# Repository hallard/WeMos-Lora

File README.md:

# ESP8266 WeMos Shield for HopeRF RFM95 RFM96 RFM98 Lora Modules

This shield is used to hold HopeRF [Lora module][4] Software with WeMos ESP8266 boards it has just few minimal features. 
- I2C Pullups placement
- Classic I2C 128x64 OLED connector
- Placement for RFM95/96/98 Lora module
- Placement for choosing single Wire, SMA or u-FL Antenna type 
- 2 x WS2812B Type LED for visual indication
- Custom switch on GPIO2
- Added footprint for Microchip 24AA02E64 64 bits serial number (v1.1+) 
- Added Solder PAD jumper to be able to connect GPIO16 to Reset to enable deep sleep (V1.2+)

You can find more information on WeMos D1 mini boards ([mini][1], [mini pro][7], [mini lite][8]), it's really well documented.
I now use WeMos boards instead of NodeMCU's one because they're just smaller, features remains the same, but I also suspect WeMos regulator far better quality than the one used on NodeMCU that are just fake of originals AMS117 3V3.

Boards arrived, I tested them, works fine with forked version of [single Channel LoRaWAN Gateway][5] but you can use any program that is compatible with RFM95 Lora module according it to real pinout.

## Detailed Description

Look at the schematics for more informations.

SPI connexion is classic (MOSI/MISO/CLK), 

**New v1.3** Solder pad on bottom layer to be able to switch 3V3 and GND Pin. It's configured as old version mapping by default (silkscreen is correct). 

Since V1.2, chip Select is still connected with GPIO16 by default but solder pad on bottom of the board allow you to connect GPIO16 to RESET for Deep Sleep. In this case: 

- add and solder R3 Pulldown (100K) to make RFM95 SPI device always selected
- on bottom solder pad cut trace between GPIO19 and SEL 
- on bottom solder join GPIO16 and RST with solder

Other pins that may need be adapted into code (for example if you use TTN network gateway code) according to the following pinout

Please not that to avoid 3 GPIOs for DIO0,DIO1,DIO2 Interrupt, these 3 are OR'ed with 3 diodes, respectively named D2,D3 and D4. This permit to use only one IRQ pin (here GPIO15). This is only possible because on IRQ routine the RFM9x IRQ register is read and then software knows which one has been triggered.
You can see more details ont this dedicated LMIC [Pull Request][6]

```
   WeMos D1          RFM9x Module
  GPIO12 (D6) <----> MISO
  GPIO13 (D7) <----> MOSI
  GPIO14 (D5) <----> CLK
  GPIO15 (D8) <----> DIO0/D2 OR DIO1/D3 OR DIO2/D4
  GPIO16 (D0) <----> SEL Chip Select (depending on bottom solder PAD position)

   WeMos D1         Shield Feature
  GPIO5  (D1) <----> I2C SCL
  GPIO4  (D2) <----> I2C SDA
  GPIO0  (D3) <----> WS2812 LEDS
  GPIO2  (D4) <----> Push Button
  GPIO16 (D0) <----> RESET (depending on bottom solder PAD position)
```

## Schematic  

## Bill Of Material

Nothing fancy, all components are 0805 and/or PTH and can be ordered almost anywhere (digikey, mouser, radiospare, ...). 
use only what you need dependings on what you want to do. You can find lot of components on ebay or aliexpress, but since vendors are often ephemere, I put for reference the BOM on well known providers.

Here is the [octopart BOM](https://octopart.com/bom-tool/SJPhS5Am)

## Firmware  

[firmware](https://github.com/hallard/WeMos-Lora/tree/master/firmware)  

## Boards  

&nbsp;

~~You can order the PCB of this board at [PCBs.io][3] if you do so, PCBs.io give me discount that allow me to buy some new created boards.~~
   
Looks like PCBs.io is gone, I do not have any rewards from PCBs.io since August 2020 and my free order placed after are still not received, so my guess they are not on business anymore.

So you can order the board on [oshpark](https://oshpark.com/shared_projects/E9P1U0Ae). It's a pitty after several discuss with OSHPark that I can't have any rewards for each people ordering my boards, this would allow me to order free PCB for shared projects and create new ones. For information my shared boards generated a total of **$285 162.00** orders at PCBs.io in 4 years, not bad at all :-)

Hoping one day OSHparks will thanks me giving them this market. 

## Assembled boards (V1.0)

## License

This work is licensed under a [Creative Commons Attribution-NonCommercial-ShareAlike 4.0 International License](https://creativecommons.org/licenses/by-nc-sa/4.0/)    
If you want to do commercial stuff with this project, please contact [CH2i company](https://www.ch2i.eu/en#support) so we can organize an simple agreement.

# Misc

See news and other projects on my [blog][2] 
 
[1]: https://wiki.wemos.cc/products:d1:d1_mini
[2]: https://hallard.me
[3]: https://PCBs.io/share/4Q1Z4 
[4]: http://www.hoperf.com/rf_transceiver/lora/
[5]: https://github.com/hallard/ESP-1ch-Gateway/
[6]: https://github.com/matthijskooijman/arduino-lmic/pull/34
[7]: https://wiki.wemos.cc/products:d1:d1_mini_pro
[8]: https://wiki.wemos.cc/products:d1:d1_mini_lite

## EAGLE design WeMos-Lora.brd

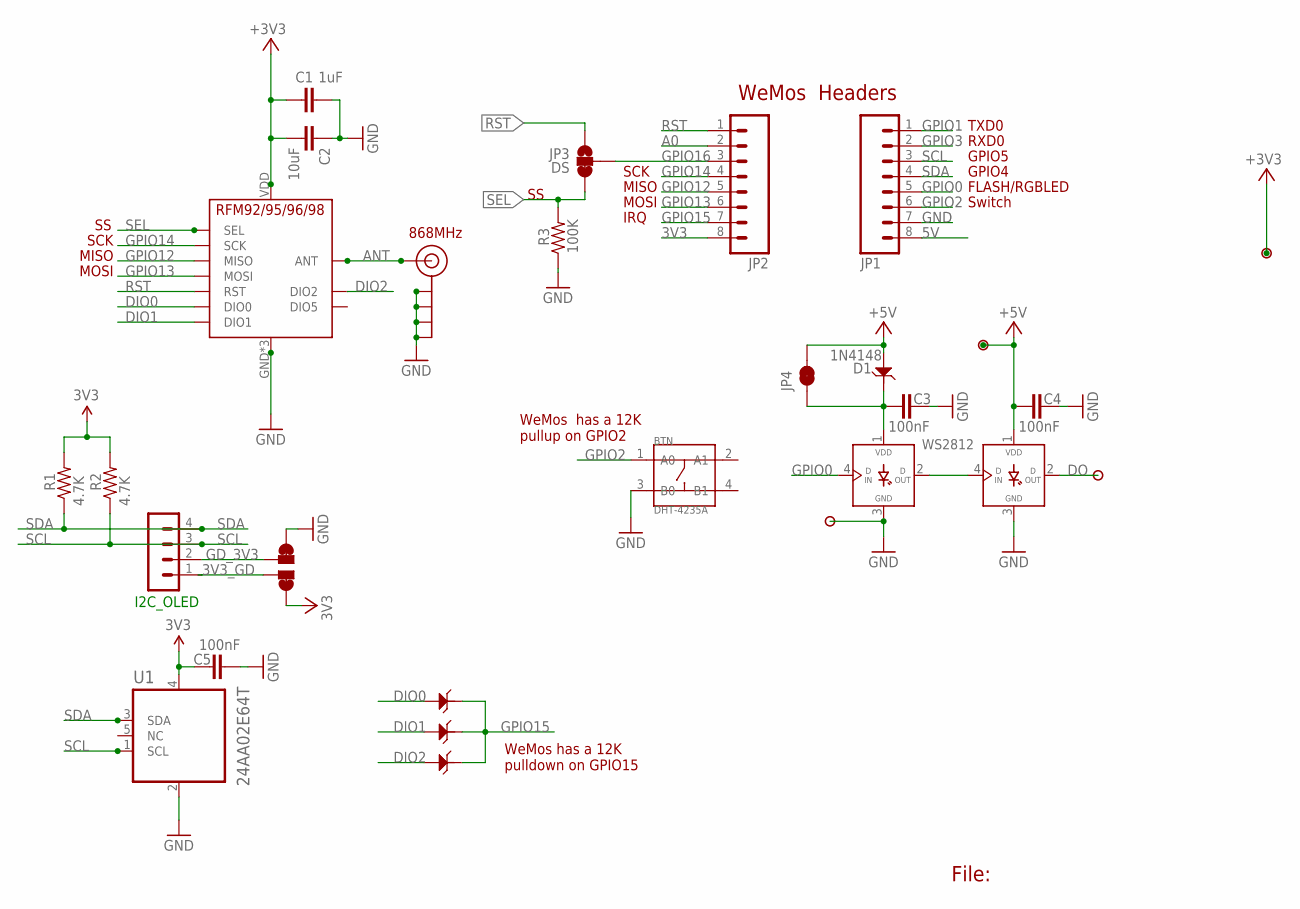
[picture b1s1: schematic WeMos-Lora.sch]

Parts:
BTN: DHT-4235A; SW4-SMD-4.2X3.2X2.5MM
C1: 1uF; 0805-CAP-LARGEPADS
C2: 10uF; 0805-CAP-LARGEPADS
C3, C4, C5: 100nF; 0805-CAP
D1, D2, D3, D4: 1N4148; SOD123-2.7X1.6
I2C_OLED: CON_HEADER_1X04'LOCK'; 1X04_LOCK
J$2: ANTENNATINY; SMA_UFL_PAD_TINY
JP1, JP2: M08NO_SILK_FEMALE_PTH; 1X08_NO_SILK
JP3: DS; PAD-JUMPER-3-2OF3_NC_BY_TRACE_YES_SILK_FULL_BOX
JP4: JUMPER-PAD-2-NC_BY_TRACE; PAD-JUMPER-2-NC_BY_TRACE_YES_SILK
P1, P2, P3, P4: PADNORMAL; PAD
R1, R2: 4.7K; 0805-RES
R3: 100K; 0805-RES
U1: 24AA02E64T; SOT95P270X145-5N
U$2: PAD-JUMPER-SWAPSWAP; PAD-JUMPER-SWAP
U$5: RFM95
WS1, WS2812: WS2812B

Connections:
3V3: C1.2, C2.2, C5.1, JP2.8, P4.1, R1.2, R2.2, U1.4 (VCC), U$2.4, U$2.44 (4), U$5.VDD (VCC)
3V3_GD: I2C_OLED.1, U$2.3
5V: C4.1, D1.1, JP1.8, JP4.2, P1.1, WS1.1 (VDD)
A0: JP2.2
ANT: J$2.ANT1 (SIGNAL), J$2.ANT2 (SIGNAL), J$2.ANT3 (SIGNAL), U$5.ANT
DIO0: D2.1, U$5.DIO0
DIO1: D3.1, U$5.DIO1
DIO2: D4.1, U$5.DIO2
DO: P2.1, WS1.2 (DOUT)
GD_3V3: I2C_OLED.2, U$2.2
GND: BTN.3 (B0), C1.1, C2.1, C3.2, C4.2, C5.2, J$2.GND1 (GND), J$2.GND2 (GND), J$2.GND3 (GND), J$2.GND4 (GND), JP1.7, P3.1, R3.1, U1.2 (VSS), U$2.1, U$2.11 (1), U$5.GND, U$5.GND1 (GND), U$5.GND2 (GND), WS1.3 (GND), WS2812.3 (GND)
GPIO0: JP1.5, WS2812.4 (DIN)
GPIO1: JP1.1
GPIO2: BTN.1 (A0), JP1.6
GPIO3: JP1.2
GPIO12: JP2.5, U$5.MISO
GPIO13: JP2.6, U$5.MOSI
GPIO14: JP2.4, U$5.SCK
GPIO15: D2.2, D3.2, D4.2, JP2.7
GPIO16: JP2.3, JP3.2
unnamed: WS1.4 (DIN), WS2812.2 (DOUT)
RST: JP2.1, JP3.1, U$5.RST
SCL: I2C_OLED.3, JP1.3, R2.1, U1.1 (SCL)
SDA: I2C_OLED.4, JP1.4, R1.1, U1.3 (SDA)
SEL: JP3.3, R3.2, U$5.NSS (SEL)
VLED: C3.1, D1.2, JP4.1, WS2812.1 (VDD)

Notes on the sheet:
File:
FLASH/RGBLED
MISO
GPIO4
GPIO5
RXD0
TXD0
MOSI
SCK
IRQ
WeMos Headers
868MHz
Switch
WeMos has a 12K pullup on GPIO2
WeMos has a 12K pulldown on GPIO15

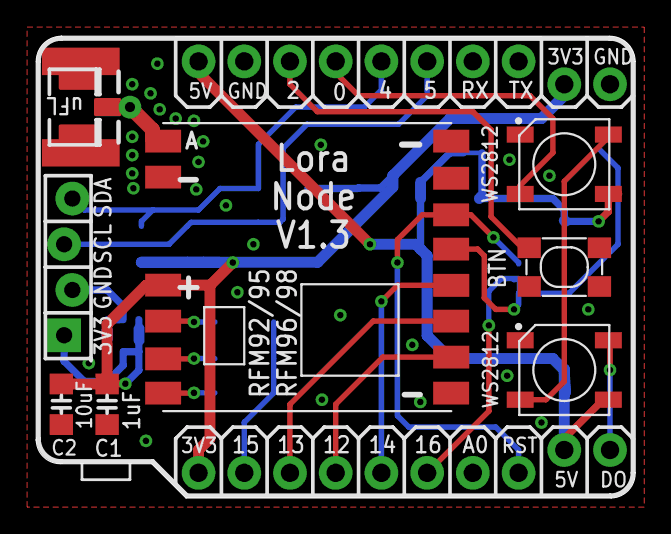
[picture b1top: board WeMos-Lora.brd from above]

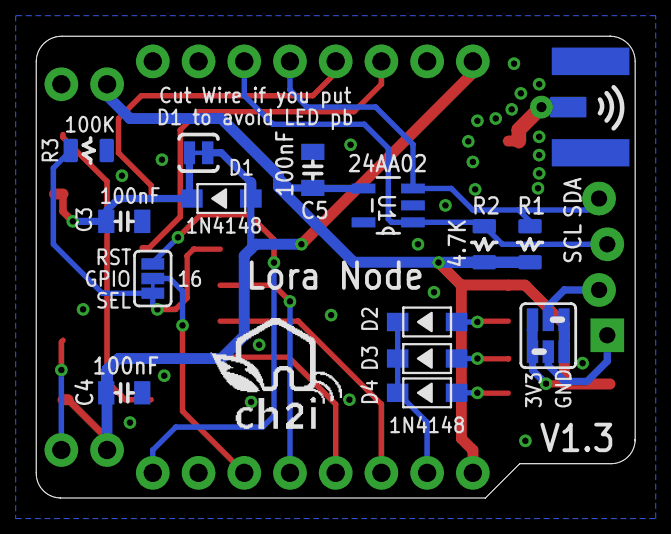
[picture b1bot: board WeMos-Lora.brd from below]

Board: 2 copper layers, 33.3 x 25.7 mm, 29 parts (15 on the bottom side), 23 nets.

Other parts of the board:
U$4: LOGO_CH2I_75MM

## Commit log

2016-04-26 Creation
2016-06-11 Added pictures and software link
2016-07-07 Moved to pictures folder
2016-07-07 Version V1.1
    - OLED Display connector has now lock pad
    - Antenna signal with via all around
    - ground plane set to 12min blocking to avoid short circuit with
    connectors in rarely cases
    - Added footprint for Microchip 24AA02E64 64 bits serial number
2016-07-07 Version V1.1
2016-07-07 fixed Broken link
2016-07-07 link
2016-09-22 Updated doc
2017-08-03 Bump to V1.2
2017-08-03 Cosmetic
2017-08-03 Updated Deep Sleep doc
2017-11-12 Updated broken link for WiMos site
2018-02-25 Bump to v1.3
2018-02-25 fixed link
2018-05-17 Added BOM
2018-05-17 Added Firmware Link
2021-01-12 Added link to OSHPark
2021-01-12 Added correct OSHPArk link
2026-04-29 Switch to CC BY-NC-SA 4.0 license, add LICENSE file

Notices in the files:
parts and their libraries:
SparkFun-Connectors: Licensing: Creative Commons ShareAlike 4.0 International - https://creativecommons.org/licenses/by-sa/4.0
